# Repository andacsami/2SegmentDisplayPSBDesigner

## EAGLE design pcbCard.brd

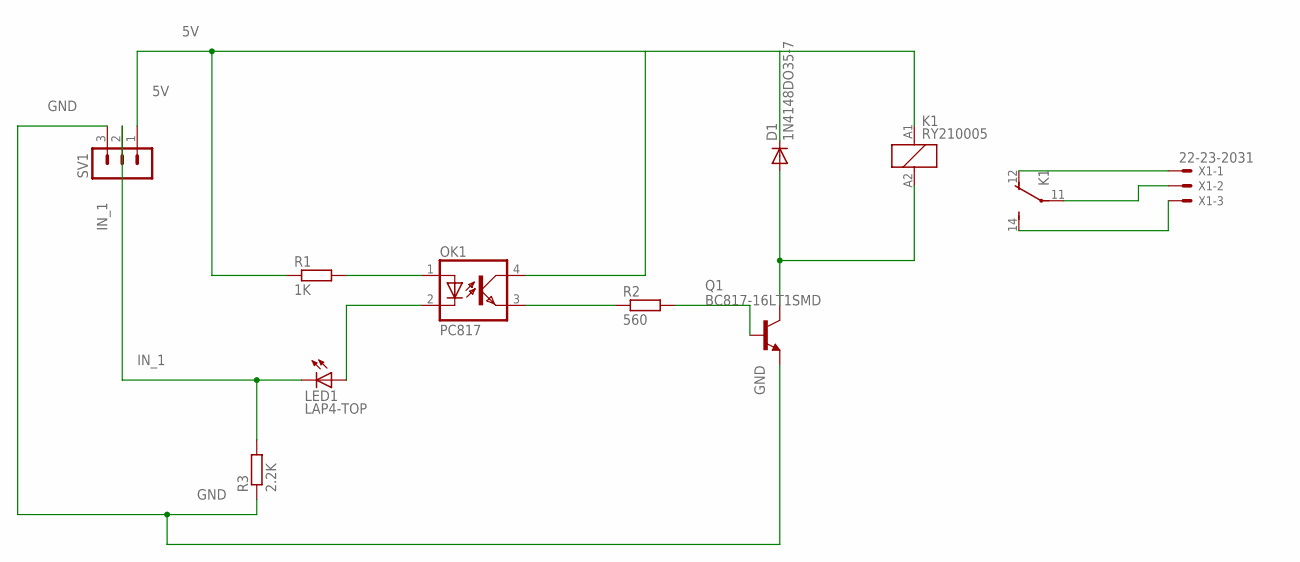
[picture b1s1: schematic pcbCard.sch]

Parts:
D1: 1N4148DO35-7; DO35-7
K1: RY210005; RY-II
LED1: LAP4-TOP; P47F-TOP
OK1: PC817; DIL04
Q1: BC817-16LT1SMD; SOT23-BEC
R1: 1K; 0204/5
R2: 560; 0204/5
R3: 2.2K; 0204/5
SV1: MA03-1
X1: 22-23-2031

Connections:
unnamed: OK1.1 (A), R1.2
unnamed: D1.A, K1.A2 (2), Q1.C
unnamed: D1.C, K1.A1 (1), OK1.4 (COL), R1.1, SV1.1
unnamed: OK1.3 (EMIT), R2.1
unnamed: Q1.B, R2.2
unnamed: LED1.A, OK1.2 (C)
unnamed: LED1.C, R3.2, SV1.2
unnamed: Q1.E, R3.1, SV1.3
unnamed: K1.12 (O), X1.1
unnamed: K1.11, X1.2
unnamed: K1.14 (S), X1.3

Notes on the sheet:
IN_1
GND

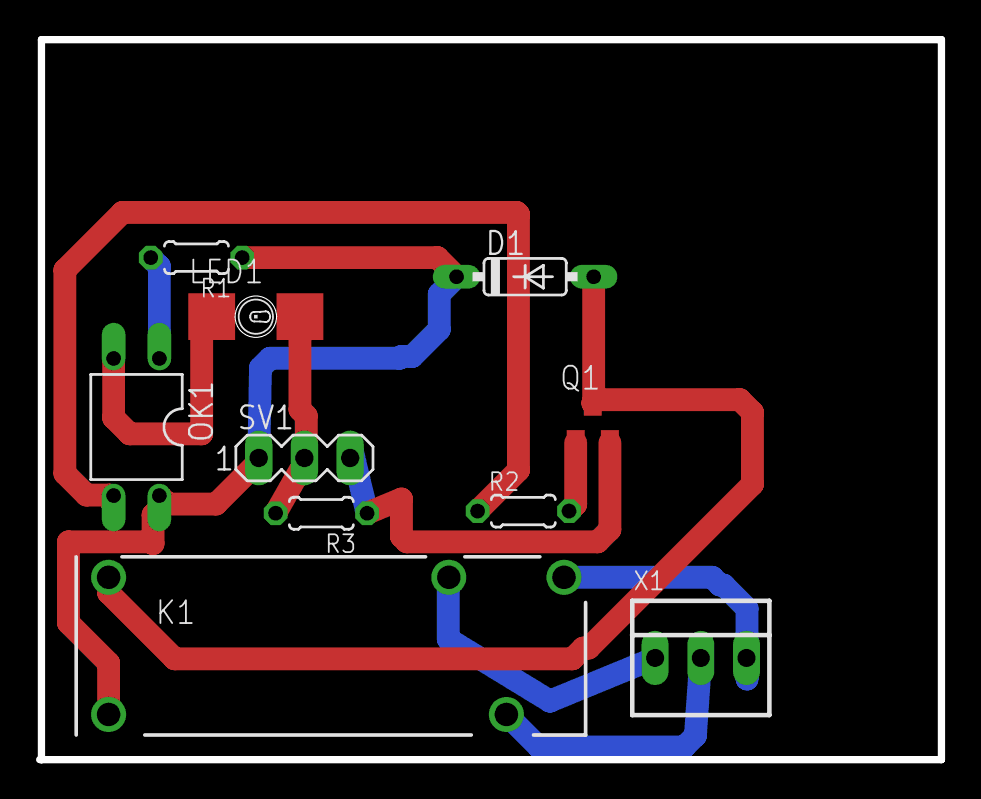
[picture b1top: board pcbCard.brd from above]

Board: 2 copper layers, 50.0 x 40.0 mm, 10 parts (0 on the bottom side), 11 nets.

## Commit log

2023-04-05 2SegmentDisplayPSBDesigner
    Çift sekment display psb kart tasarımı.
